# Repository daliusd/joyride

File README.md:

# joyride keyboard

This is my attempt to build keyboard with joysticks.

3D simulation:

Photo of assembled keyboard:

NOTE: ⚠️ This is first version, so there are issues with it ⚠️

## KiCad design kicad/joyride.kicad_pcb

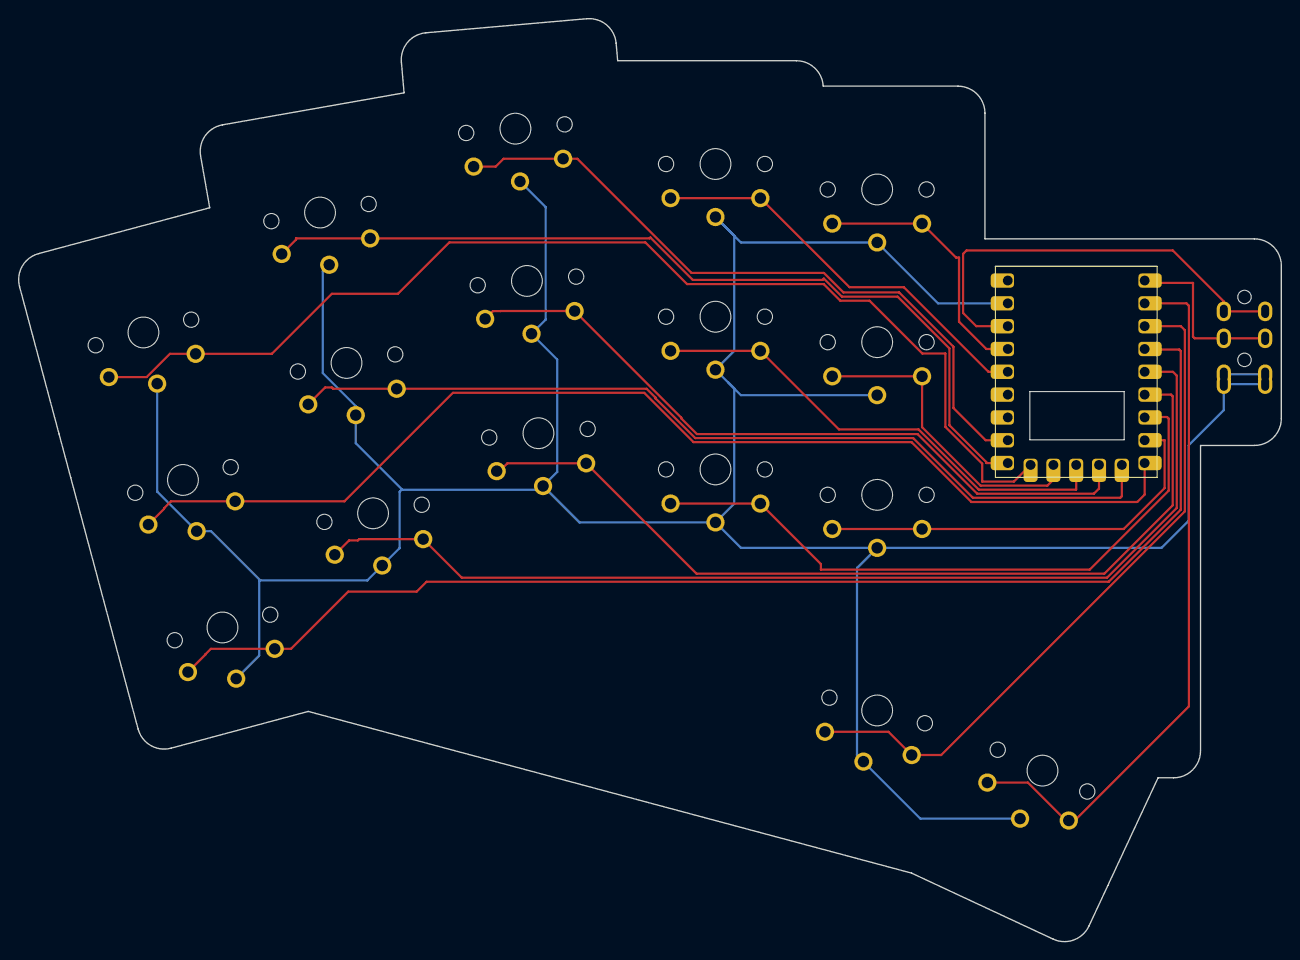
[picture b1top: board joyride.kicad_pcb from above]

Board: 2 copper layers, 140.6 x 102.8 mm, 19 parts (0 on the bottom side), 20 nets.

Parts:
RP2040Zero1: RP2040-Zero
S1, S2, S3, S4, S5, S6, S7, S8, S9, S10, S11, S12, S13, S14, S15, S16, S17: PG1350
TRRS1: TRRS-PJ-320A-dual

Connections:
GND: RP2040Zero1.20, S1.2, S2.2, S3.2, S4.2, S5.2, S6.2, S7.2, S8.2, S9.2, S10.2, S11.2, S12.2, S13.2, S14.2, S15.2, S16.2, S17.2, TRRS1.1, TRRS1.2
GP0: RP2040Zero1.1, TRRS1.3
GP1: RP2040Zero1.2, S17.1
GP2: RP2040Zero1.3, S16.1
GP3: RP2040Zero1.4, S1.1
GP4: RP2040Zero1.5, S4.1
GP5: RP2040Zero1.6, S7.1
GP6: RP2040Zero1.7, S10.1
GP7: RP2040Zero1.8, S13.1
GP8: RP2040Zero1.9, S2.1
GP9: RP2040Zero1.10, S5.1
GP10: RP2040Zero1.11, S8.1
GP11: RP2040Zero1.12, S11.1
GP12: RP2040Zero1.13, S14.1
GP13: RP2040Zero1.14, S3.1
GP14: RP2040Zero1.15, S6.1
GP15: RP2040Zero1.16, S9.1
GP28: RP2040Zero1.22, S12.1
GP29: RP2040Zero1.23, S15.1
P3V3: RP2040Zero1.21, TRRS1.4

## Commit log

2023-10-13 Joyride initial version
2023-10-13 LICENSE added
2023-10-13 README added
2023-10-29 Photo added.
2023-10-29 Image link fix.
